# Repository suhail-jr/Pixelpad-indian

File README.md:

# Pixelpad-indian
Pixelpad indian is an opensource electronic development badge based atmega 32u4 and the PCB art is inspired from indian cultural arts and paintings.

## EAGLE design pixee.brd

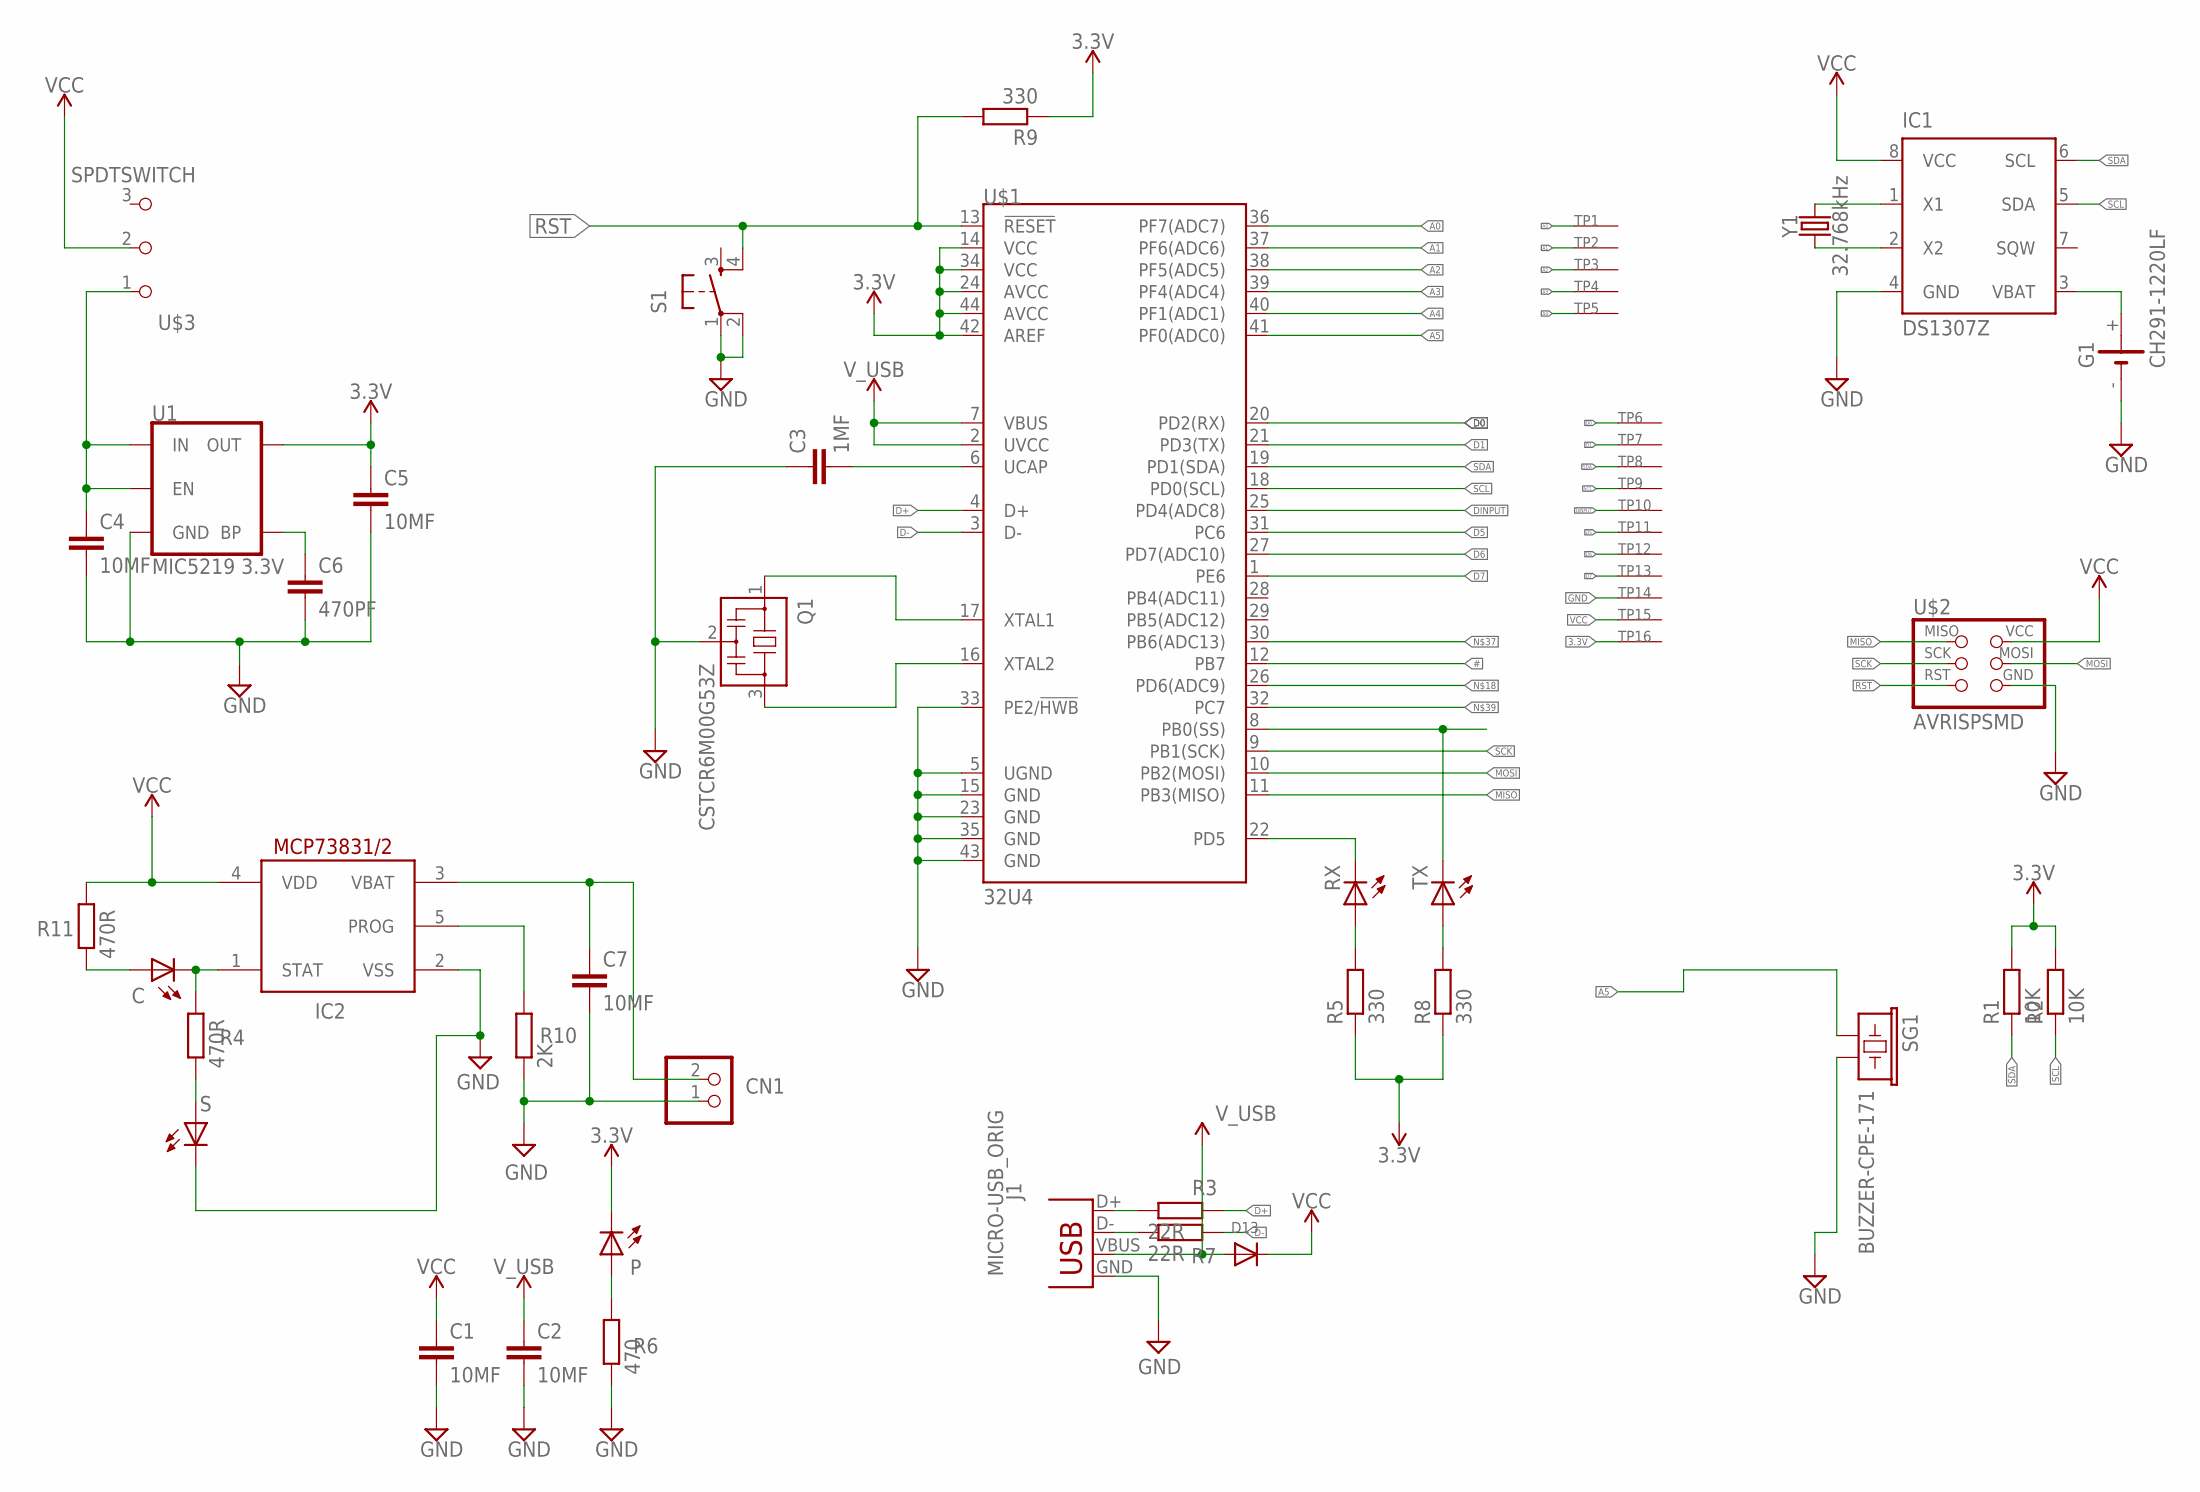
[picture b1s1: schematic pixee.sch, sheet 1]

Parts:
C: LEDCHIP-LED0805; CHIP-LED0805
C1, C2, C4, C5, C7: 10MF; C0603
C3: 1MF; C0603
C6: 470PF; C0603
CN1: JST_2PIN-SMT; JST-PH-2-SMT
D13: DIODESOD-123; SOD-123
G1: CH291-1220LF
IC1: DS1307Z; SOIC8
IC2: MCP73831/OT; SOT23-5L
J1: MICRO-USB_ORIG; DX4R005HJ5
P: LEDCHIP-LED0805; CHIP-LED0805
Q1: CSTCR6M00G53Z; CSTCR6M
R1, R2: 10K; M0805
R3, R7: 22R; M0805
R4, R11: 470R; M0805
R5, R8, R9: 330; M0805
R6: 470; M0805
R10: 2K; M0805
RX: LEDCHIP-LED0805; CHIP-LED0805
S: LEDCHIP-LED0805; CHIP-LED0805
S1: 6MM_SWITCH6MM_SWITCH; 6MM_SWITCH
SG1: BUZZER-CPE-171; BUZZER_9MM_PTH
TP1, TP2, TP3, TP4, TP5, TP6, TP7, TP8, TP9, TP10, TP11, TP12, TP13, TP14, TP15, TP16: SEWTAP-2.0IN; SEWINGTAP_2.0
TX: LEDCHIP-LED0805; CHIP-LED0805
U1: MIC5219 3.3V; SOT23-5
U$1: 32U4; TQFP44
U$2: AVRISPSMD; 2X03SMD
U$3: SPDTSWITCH
Y1: 32.768kHz; CRYSTAL-PTH-2X6-CYL

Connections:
3.3V: C5.1, P.C, R1.2, R2.2, R5.1, R8.1, R9.1, TP16.P$1, U1.5 (OUT), U$1.14 (VCC), U$1.24 (AVCC), U$1.34 (VCC), U$1.42 (AREF), U$1.44 (AVCC)
#: U$1.12 (PB7)
A0: TP1.P$1, U$1.36 (PF7(ADC7))
A1: TP2.P$1, U$1.37 (PF6(ADC6))
A2: TP3.P$1, U$1.38 (PF5(ADC5))
A3: TP4.P$1, U$1.39 (PF4(ADC4))
A4: TP5.P$1, U$1.40 (PF1(ADC1))
A5: SG1.P$1 (1), U$1.41 (PF0(ADC0))
D0: TP6.P$1, U$1.20 (PD2(RX))
D1: TP7.P$1, U$1.21 (PD3(TX))
D5: TP11.P$1, U$1.31 (PC6)
D6: TP12.P$1, U$1.27 (PD7(ADC10))
D7: TP13.P$1, U$1.1 (PE6)
D+: R3.2, U$1.4 (D+)
D-: R7.2, U$1.3 (D-)
DINPUT: TP10.P$1, U$1.25 (PD4(ADC8)); also elsewhere on the board
GND: C1.2, C2.2, C3.1, C4.2, C5.2, C6.2, C7.2, CN1.1 (2), G1.-, IC1.4 (GND), IC2.2 (VSS), J1.GND, Q1.2, R6.1, R10.1, S.C, S1.1, S1.2 (P1), SG1.P$2 (2), TP14.P$1, U1.2 (GND), U$1.5 (UGND), U$1.15 (GND), U$1.23 (GND), U$1.33 (PE2/!HWB), U$1.35 (GND), U$1.43 (GND), U$2.6 (GND); also elsewhere on the board
MISO: U$1.11 (PB3(MISO)), U$2.1 (MISO)
MOSI: U$1.10 (PB2(MOSI)), U$2.4 (MOSI)
unnamed: C3.2, U$1.6 (UCAP)
unnamed: Q1.1, U$1.17 (XTAL1)
unnamed: Q1.3, U$1.16 (XTAL2)
unnamed: IC1.1 (X1), Y1.2
unnamed: IC1.2 (X2), Y1.1
unnamed: G1.+, IC1.3 (VBAT)
unnamed: C.C, IC2.1 (STAT), R4.2
unnamed: IC2.5 (PROG), R10.2
unnamed: P.A, R6.2
unnamed: C.A, R11.1
unnamed: R4.1, S.A
unnamed: C7.1, CN1.2 (1), IC2.3 (VBAT)
unnamed: J1.D+, R3.1
unnamed: C6.1, U1.4 (BP)
unnamed: J1.D-, R7.1
unnamed: C4.1, U1.1 (IN), U1.3 (EN), U$3.1
unnamed: RX.C, U$1.22 (PD5)
unnamed: R5.2, RX.A
unnamed: R8.2, TX.A
unnamed: TX.C, U$1.8 (PB0(SS))
RST: R9.2, S1.4 (S1), U$1.13 (!RESET), U$2.5 (RST)
SCK: U$1.9 (PB1(SCK)), U$2.3 (SCK)
SCL: IC1.5 (SDA), R2.1, TP9.P$1, U$1.18 (PD0(SCL))
SDA: IC1.6 (SCL), R1.1, TP8.P$1, U$1.19 (PD1(SDA))
VCC: C1.1, D13.C, IC1.8 (VCC), IC2.4 (VDD), R11.2, TP15.P$1, U$2.2 (VCC), U$3.2; also elsewhere on the board
V_USB: C2.1, D13.A, J1.VBUS, U$1.2 (UVCC), U$1.7 (VBUS)

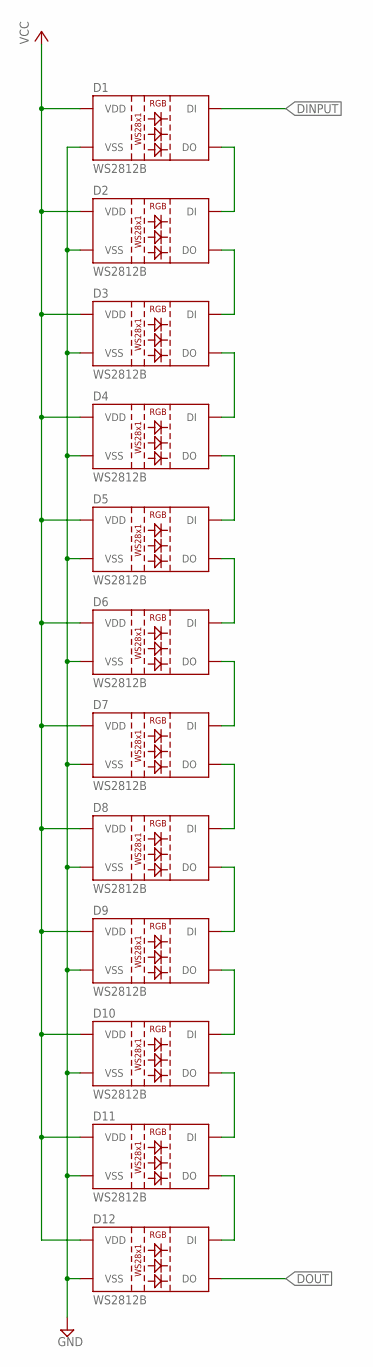
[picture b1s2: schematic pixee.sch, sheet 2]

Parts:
D1, D2, D3, D4, D5, D6, D7, D8, D9, D10, D11, D12: WS2812B

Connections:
DINPUT: D1.4 (DI); also elsewhere on the board
DOUT: D12.2 (DO)
GND: D1.3 (VSS), D2.3 (VSS), D3.3 (VSS), D4.3 (VSS), D5.3 (VSS), D6.3 (VSS), D7.3 (VSS), D8.3 (VSS), D9.3 (VSS), D10.3 (VSS), D11.3 (VSS), D12.3 (VSS); also elsewhere on the board
unnamed: D1.2 (DO), D2.4 (DI)
unnamed: D2.2 (DO), D3.4 (DI)
unnamed: D3.2 (DO), D4.4 (DI)
unnamed: D4.2 (DO), D5.4 (DI)
unnamed: D5.2 (DO), D6.4 (DI)
unnamed: D6.2 (DO), D7.4 (DI)
unnamed: D7.2 (DO), D8.4 (DI)
unnamed: D8.2 (DO), D9.4 (DI)
unnamed: D9.2 (DO), D10.4 (DI)
unnamed: D10.2 (DO), D11.4 (DI)
unnamed: D11.2 (DO), D12.4 (DI)
VCC: D1.1 (VDD), D2.1 (VDD), D3.1 (VDD), D4.1 (VDD), D5.1 (VDD), D6.1 (VDD), D7.1 (VDD), D8.1 (VDD), D9.1 (VDD), D10.1 (VDD), D11.1 (VDD), D12.1 (VDD); also elsewhere on the board

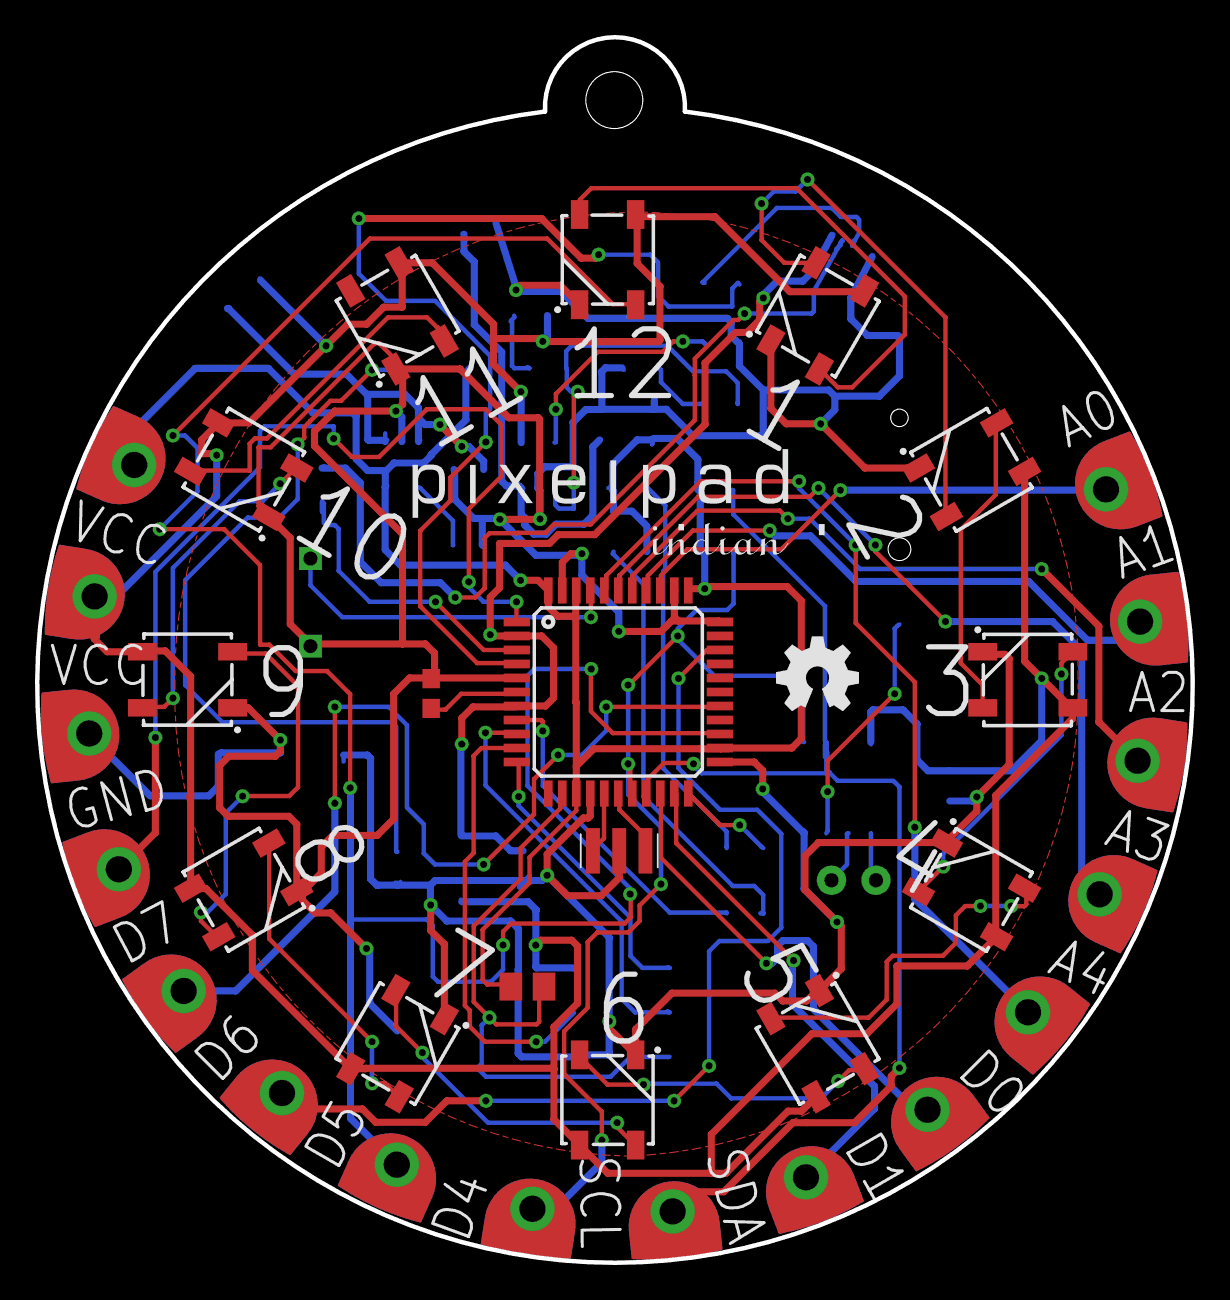
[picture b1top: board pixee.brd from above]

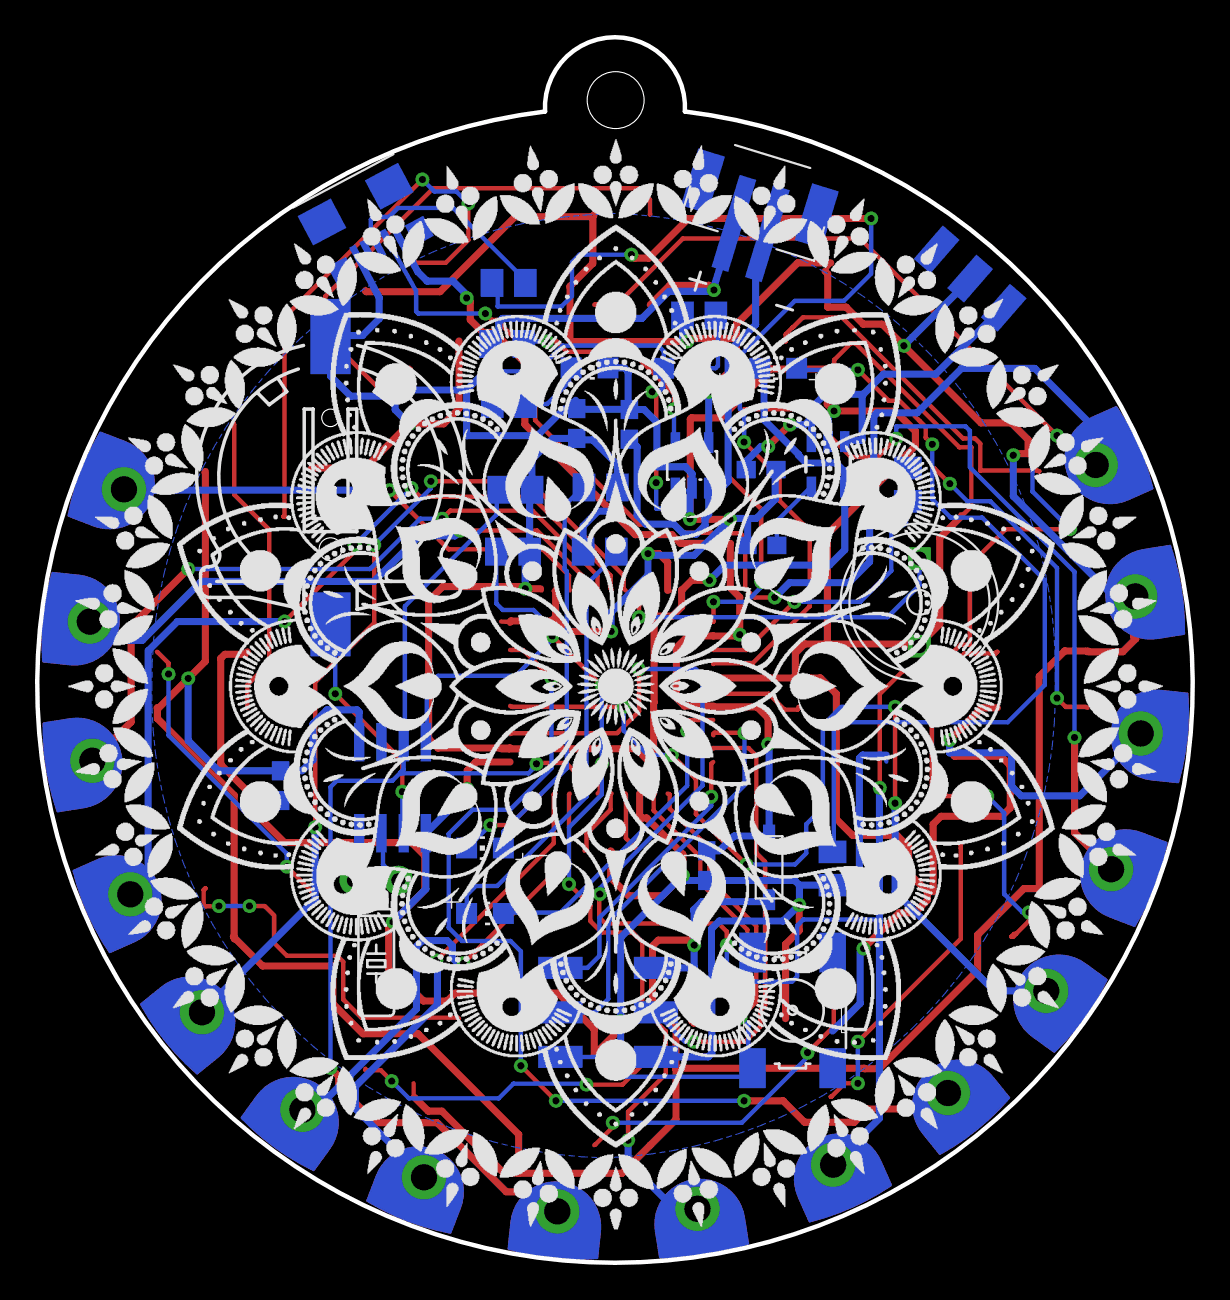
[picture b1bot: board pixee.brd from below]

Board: 2 copper layers, 66.0 x 70.0 mm, 65 parts (33 on the bottom side), 55 nets.

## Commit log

2020-04-17 Create LICENSE

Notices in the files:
parts and their libraries:
SparkFun-LED: Licensing: Creative Commons ShareAlike 4.0 International - https://creativecommons.org/licenses/by-sa/4.0
